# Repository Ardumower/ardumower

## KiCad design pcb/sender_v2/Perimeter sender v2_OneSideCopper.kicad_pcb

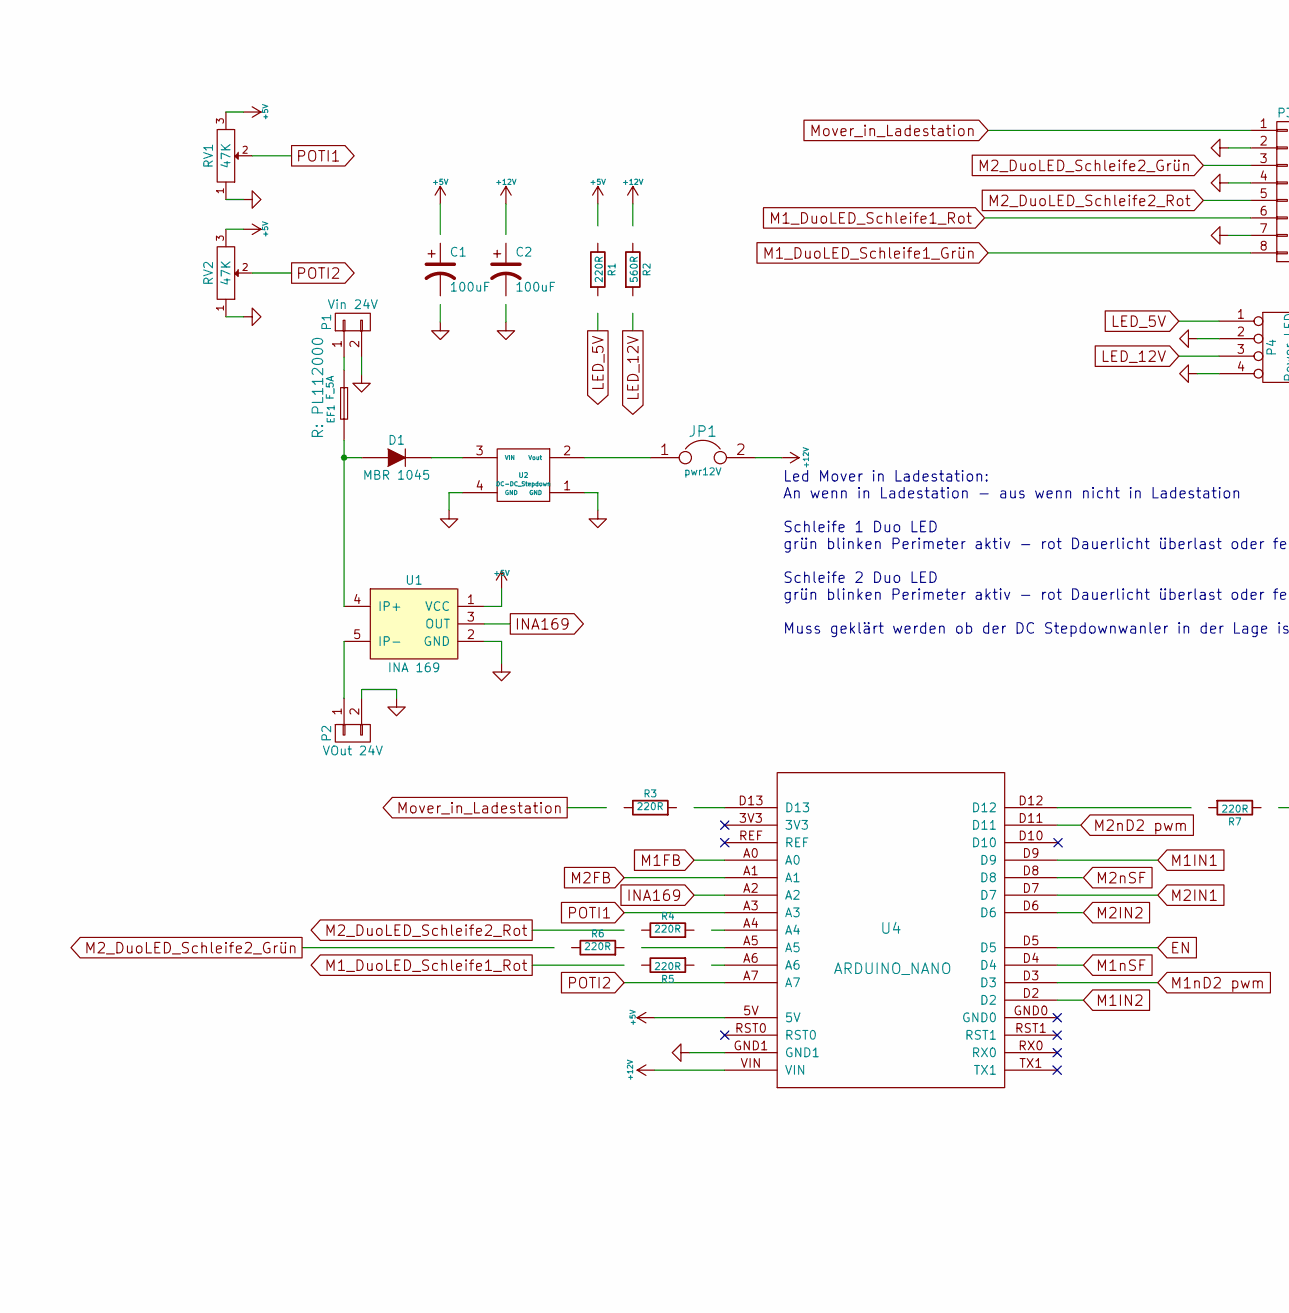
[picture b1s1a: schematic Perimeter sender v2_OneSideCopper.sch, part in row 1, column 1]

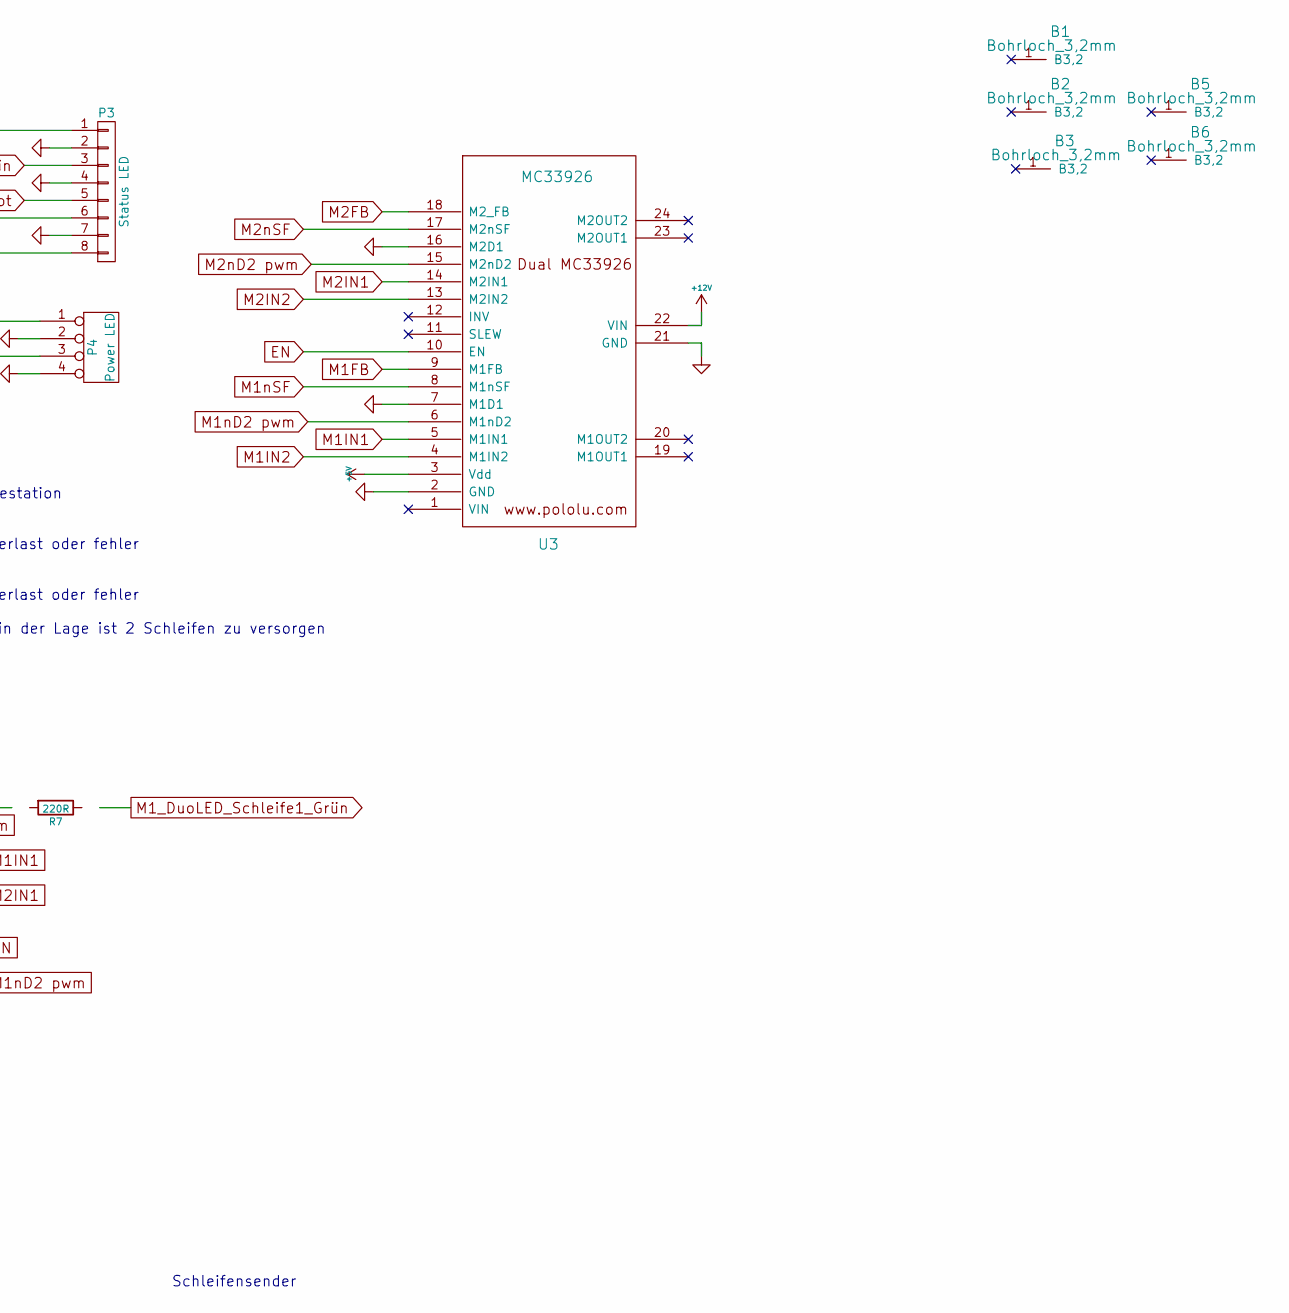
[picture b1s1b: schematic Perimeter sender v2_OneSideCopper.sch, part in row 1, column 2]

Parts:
B1, B2, B3, B5, B6: Bohrloch_3,2mm
C1, C2: 100uF; Elko_vert_11.2x6.3mm_RM2.5_RM5.0
D1: MBR 1045; MBR1045_Horizontal
EF1: F_5A; Fuseholder_Reichelt_PL112000
JP1: pwr12V; Pin_Header_Straight_1x02
P1: Vin 24V; Anschlussklemme_2P_RM5,08
P2: VOut 24V; Anschlussklemme_2P_RM5,08
P3: Status LED; Pin_Header_Straight_1x08
P4: Power LED; Pin_Header_Straight_1x04
R1, R3, R4, R5, R6, R7: 220R; Resistor_Horizontal_RM10mm
R2: 560R; Resistor_Horizontal_RM10mm
RV1, RV2: 47K; Potentiometer_VishaySpectrol-Econtrim-Type36T_3D-angepasst_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
U1: INA 169; INA169
U2: DC-DC_Stepdown; DC_DC_DSN2596_mit_Bohrloch
U3: MC33926; MC_33926_31polig_mit_Bohrloch_neue_Masse
U4: ARDUINO_NANO; arduino_nano

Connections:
+5V: C1.1, R1.1, RV1.3, RV2.3, U1.1 (VCC), U3.3 (Vdd), U4.5V
+12V: C2.1, JP1.2, R2.1, U3.22 (VIN), U4.VIN
EN: U3.10 (EN), U4.D5
GND: C1.2, C2.2, P1.2, P2.2, P3.2, P3.4, P3.7, P4.2, P4.4, RV1.1, RV2.1, U1.2 (GND), U2.1 (GND), U2.4 (GND), U3.2 (GND), U3.7 (M1D1), U3.16 (M2D1), U3.21 (GND), U4.GND1
INA169: U1.3 (OUT), U4.A2
LED_5V: P4.1, R1.2
LED_12V: P4.3, R2.2
M1FB: U3.9 (M1FB), U4.A0
M1IN1: U3.5 (M1IN1), U4.D9
M1IN2: U3.4 (M1IN2), U4.D2
M1_DuoLED_Schleife1_Grün: P3.8, R7.1
M1_DuoLED_Schleife1_Rot: P3.6, R5.1
M1nD2 pwm: U3.6 (M1nD2), U4.D3
M1nSF: U3.8 (M1nSF), U4.D4
M2FB: U3.18 (M2_FB), U4.A1
M2IN1: U3.14 (M2IN1), U4.D7
M2IN2: U3.13 (M2IN2), U4.D6
M2_DuoLED_Schleife2_Grün: P3.3, R6.1
M2_DuoLED_Schleife2_Rot: P3.5, R4.1
M2nD2 pwm: U3.15 (M2nD2), U4.D11
M2nSF: U3.17 (M2nSF), U4.D8
Mover_in_Ladestation: P3.1, R3.1
unnamed: D1.1 (A), EF1.1, U1.4 (IP+)
unnamed: D1.2 (K), U2.3 (VIN)
unnamed: EF1.2, P1.1
unnamed: JP1.1, U2.2 (Vout)
unnamed: P2.1, U1.5 (IP-)
unnamed: R3.2, U4.D13
unnamed: R4.2, U4.A4
unnamed: R5.2, U4.A6
unnamed: R6.2, U4.A5
unnamed: R7.2, U4.D12
POTI1: RV1.2, U4.A3
POTI2: RV2.2, U4.A7

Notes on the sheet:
Led Mover in Ladestation: An wenn in Ladestation - aus wenn nicht in Ladestation Schleife 1 Duo LED grün blinken Perimeter aktiv - rot Dauerlicht überlast oder fehler Schleife 2 Duo LED grün blinken Perimeter aktiv - rot Dauerlicht überlast oder fehler Muss geklärt werden ob der DC Stepdownwanler i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
Schleifensender

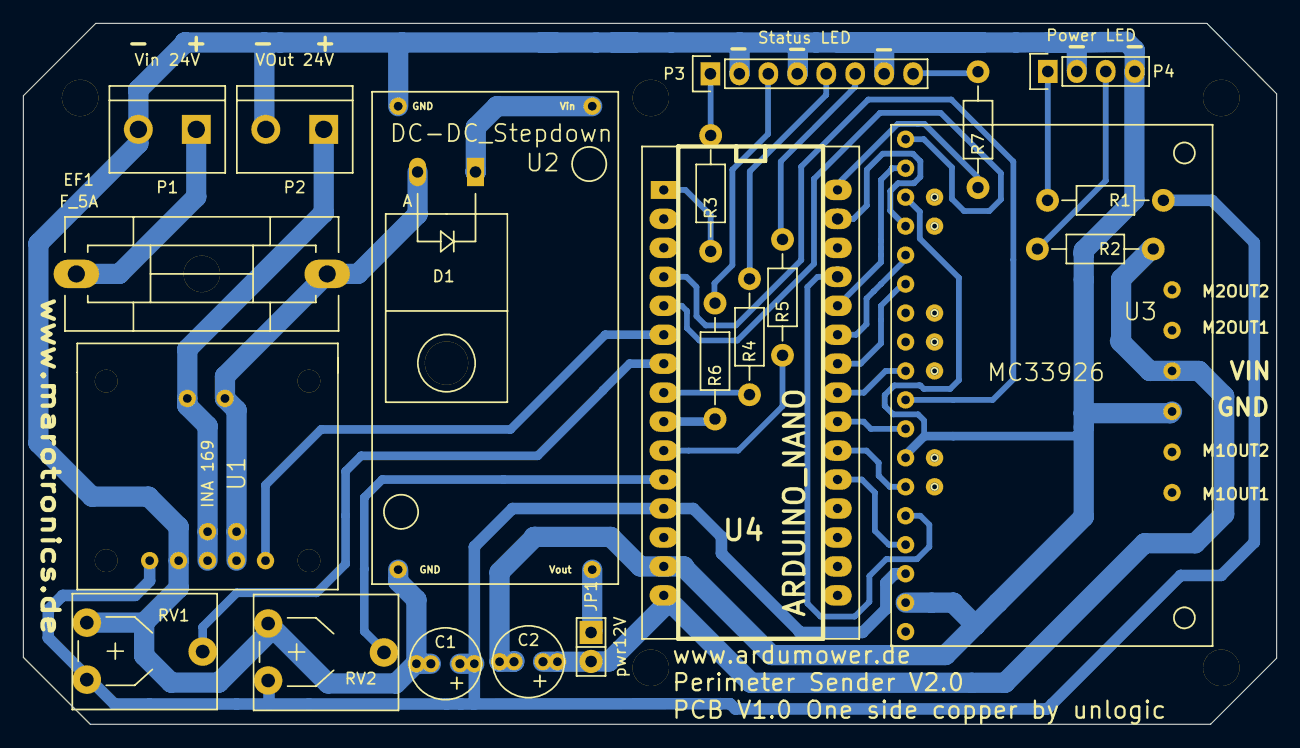
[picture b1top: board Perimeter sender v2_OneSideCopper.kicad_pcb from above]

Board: 2 copper layers, 109.9 x 61.5 mm, 27 parts (0 on the bottom side), 34 nets.

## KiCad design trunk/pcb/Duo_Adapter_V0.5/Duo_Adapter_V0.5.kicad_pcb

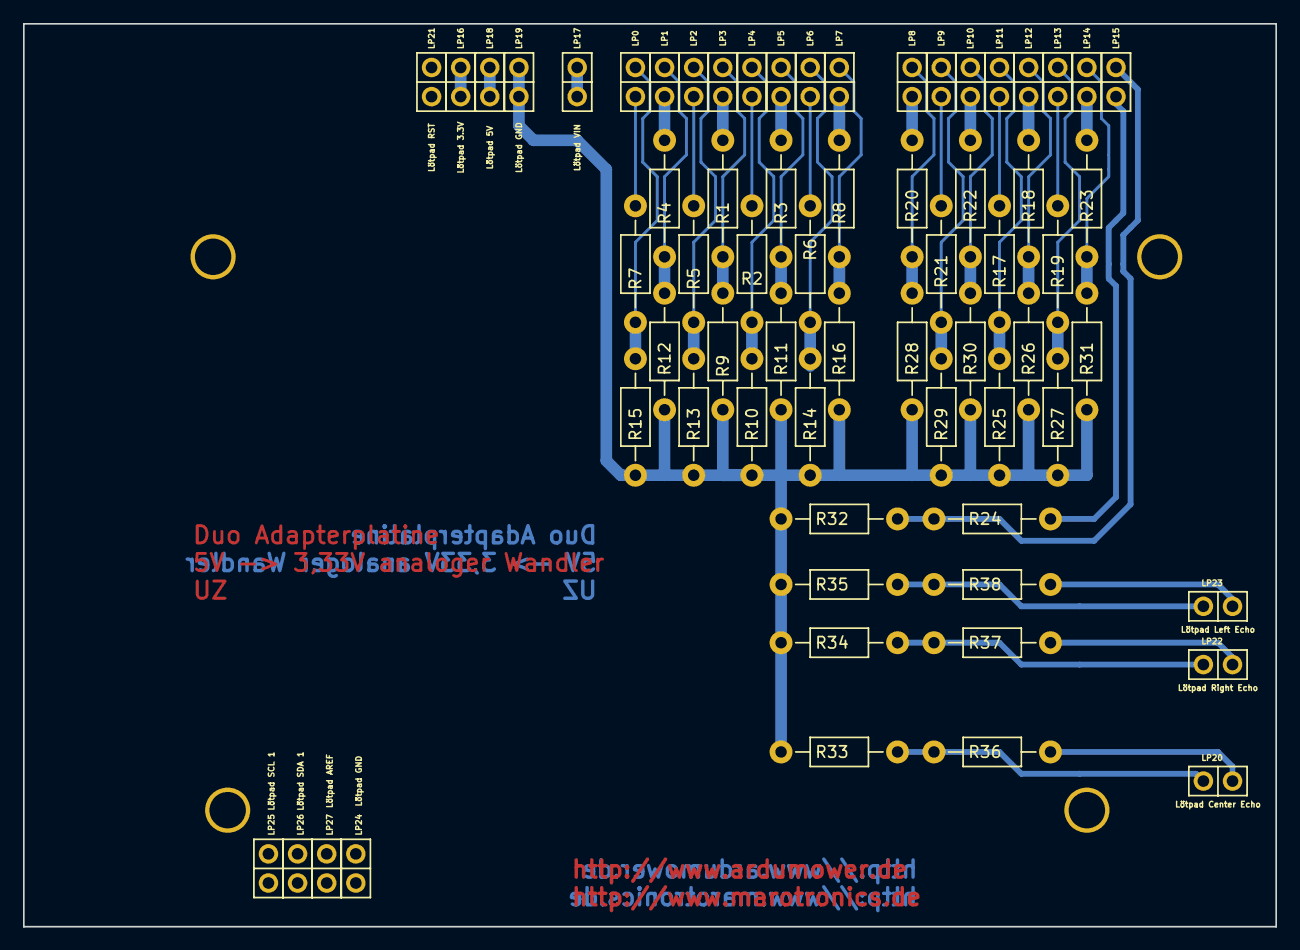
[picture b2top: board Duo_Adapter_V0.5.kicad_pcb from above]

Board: 2 copper layers, 109.2 x 78.7 mm, 67 parts (1 on the bottom side), 42 nets.

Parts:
LP0, LP1, LP2, LP3, LP4, LP5, LP6, LP7, LP8, LP9, LP10, LP11, LP12, LP13, LP14, LP15: Lötpad; Lötpad_1x02_Buchse
LP16: Lötpad 3.3V; Lötpad_1x02_Buchse
LP17: Lötpad VIN; Lötpad_1x02_Buchse
LP18: Lötpad 5V; Lötpad_1x02_Buchse
LP19, LP24: Lötpad GND; Lötpad_1x02_Buchse
LP20: Lötpad Center Echo; Lötpad_1x02_Buchse
LP21: Lötpad RST; Lötpad_1x02_Buchse
LP22: Lötpad Right Echo; Lötpad_1x02_Buchse
LP23: Lötpad Left Echo; Lötpad_1x02_Buchse
LP25: Lötpad SCL 1; Lötpad_1x02_Buchse
LP26: Lötpad SDA 1; Lötpad_1x02_Buchse
LP27: Lötpad AREF; Lötpad_1x02_Buchse
R1, R2, R3, R4, R5, R6, R7, R8, R17, R18, R19, R20, R21, R22, R23, R24, R36, R37, R38: R 10K; Resistor_Horizontal_RM10mm
R9, R10, R11, R12, R13, R14, R15, R16, R25, R26, R27, R28, R29, R30, R31, R32, R33, R34, R35: R 20K; Resistor_Horizontal_RM10mm
SHIELD1: ARDUINO_MEGA_SHIELD; ARDUINO_MEGA_SHIELD_DUO_3D

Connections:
+3V3: LP16.1, LP16.2
+5V: LP18.1, LP18.2
GND: LP19.1, LP19.2, R9.2, R10.2, R11.2, R12.2, R13.2, R14.2, R15.2, R16.2, R25.2, R26.2, R27.2, R28.2, R29.2, R30.2, R31.2, R32.2, R33.2, R34.2, R35.2
unnamed: LP0.1, R7.1
unnamed: LP0.2, R7.2, R15.1
unnamed: LP1.1, R4.1
unnamed: LP1.2, R4.2, R12.1
unnamed: LP2.1, R5.1
unnamed: LP2.2, R5.2, R13.1
unnamed: LP3.1, R1.1
unnamed: LP3.2, R1.2, R9.1
unnamed: LP4.1, R2.1
unnamed: LP4.2, R2.2, R10.1
unnamed: LP5.1, R3.1
unnamed: LP5.2, R3.2, R11.1
unnamed: LP6.1, R6.1
unnamed: LP6.2, R6.2, R14.1
unnamed: LP7.1, R8.1
unnamed: LP7.2, R8.2, R16.1
unnamed: LP8.1, R20.1
unnamed: LP8.2, R20.2, R28.1
unnamed: LP9.1, R21.1
unnamed: LP9.2, R21.2, R29.1
unnamed: LP10.1, R22.1
unnamed: LP10.2, R22.2, R30.1
unnamed: LP11.1, R17.1
unnamed: LP11.2, R17.2, R25.1
unnamed: LP12.1, R18.1
unnamed: LP12.2, R18.2, R26.1
unnamed: LP13.1, R19.1
unnamed: LP13.2, R19.2, R27.1
unnamed: LP14.1, R23.1
unnamed: LP14.2, R23.2, R31.1
unnamed: LP15.1, R24.1
unnamed: LP15.2, R24.2, R32.1
unnamed: LP17.1, LP17.2
unnamed: LP20.1, R33.1, R36.2
unnamed: LP20.2, R36.1
unnamed: LP22.1, R34.1, R37.2
unnamed: LP22.2, R37.1
unnamed: LP23.1, R35.1, R38.2
unnamed: LP23.2, R38.1

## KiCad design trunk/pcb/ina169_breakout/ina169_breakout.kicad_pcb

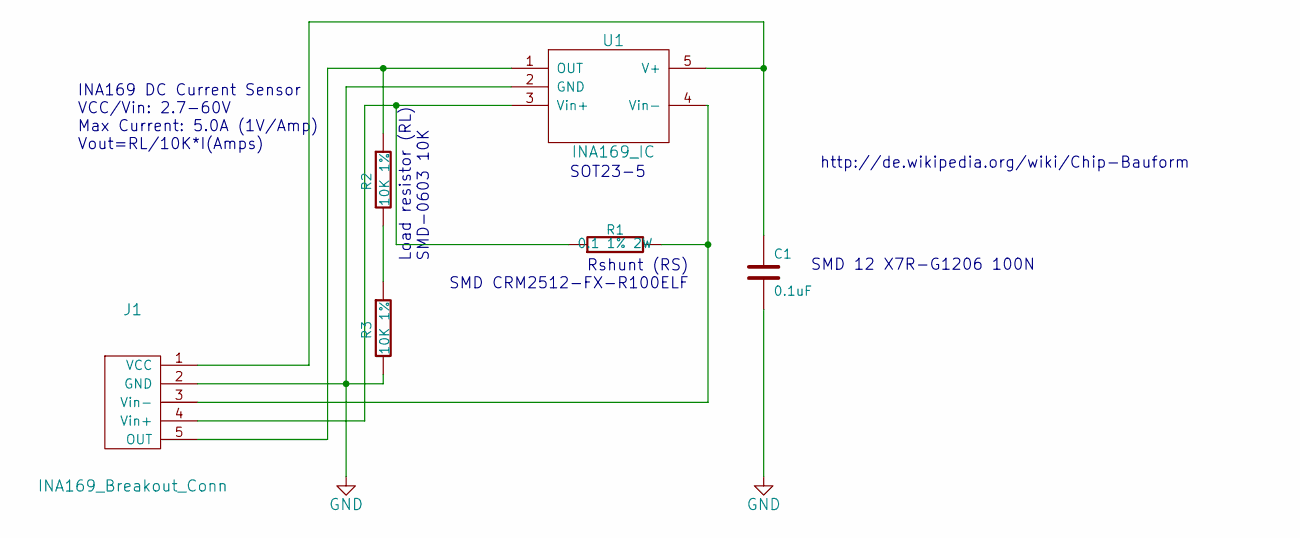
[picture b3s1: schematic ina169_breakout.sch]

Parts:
C1: 0.1uF; C_1206
J1: INA169_Breakout_Conn; ina169_breakout_footprint
R1: 0.1 1% 2W; R_2512
R2, R3: 10K 1%; R_0603
U1: INA169_IC; ina169_ic_sot23-5

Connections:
GND: C1.2, J1.2 (GND), R3.2, U1.2 (GND)
unnamed: C1.1, J1.1 (VCC), U1.5 (V+)
unnamed: J1.3 (Vin-), R1.2, U1.4 (Vin-)
unnamed: J1.4 (Vin+), R1.1, U1.3 (Vin+)
unnamed: J1.5 (OUT), R2.1, U1.1 (OUT)
unnamed: R2.2, R3.1

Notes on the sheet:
Rshunt (RS) SMD CRM2512-FX-R100ELF
Load resistor (RL) SMD-0603 10K
INA169 DC Current Sensor VCC/Vin: 2.7-60V Max Current: 5.0A (1V/Amp) Vout=RL/10K*I(Amps)
SMD 12 X7R-G1206 100N
SOT23-5
http://de.wikipedia.org/wiki/Chip-Bauform

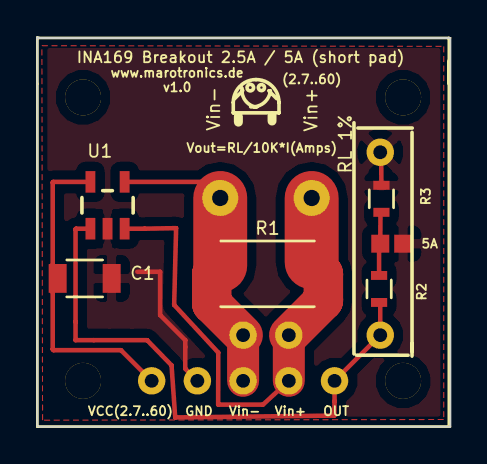
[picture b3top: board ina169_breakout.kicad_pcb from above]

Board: 2 copper layers, 23.0 x 21.7 mm, 6 parts (0 on the bottom side), 6 nets.

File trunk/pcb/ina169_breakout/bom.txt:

C1  0.1uF  1206   SMD 12 X7R-G1206 100N        
R1  0.1  1%  2W   2512  SMD CRM2512-FX-R100ELF  
R2,R3   10K  1%   0603  
U1   INA169 SOT23-5

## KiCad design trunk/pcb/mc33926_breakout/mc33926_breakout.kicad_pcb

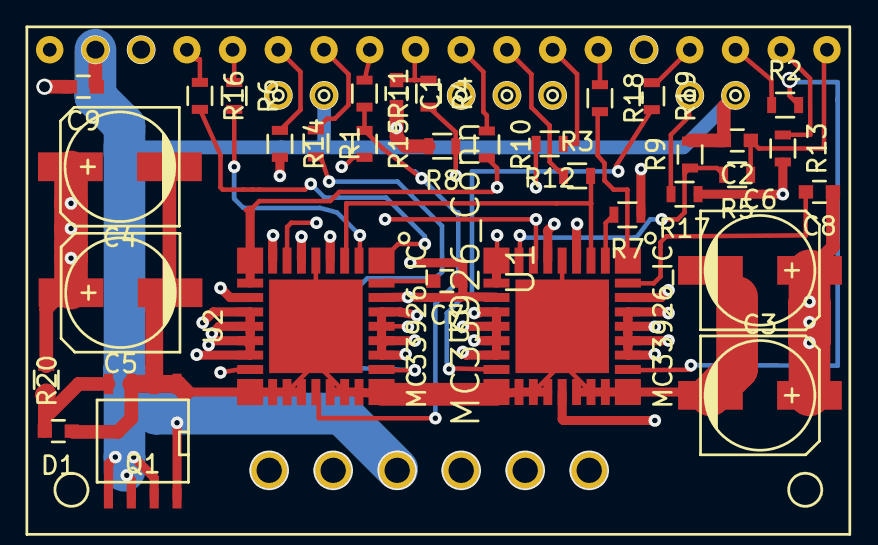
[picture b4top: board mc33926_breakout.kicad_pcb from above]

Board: 4 copper layers, 34 parts (0 on the bottom side), 41 nets.

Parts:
C1, C2: 0.47uF; C_0603
C3, C4, C5, C6: 47uF; c_elec_6.3x5.8
C7, C8: 33nF; C_0603
C9: 0.1uF; C_0603
D1: ZENER; C_0603
Q1: MOSN-SO8; SOIC-8-N
R1, R2, R3, R4, R5, R6, R7, R10, R11, R12, R13, R14, R16, R18, R19: 1k; R_0603
R8, R9: 220; R_0603
R15, R17: 10k; R_0603
R20: 100k; R_0603
U1: MC33926_Conn; mc33926_breakout_footprint
U2, U3: MC33926_IC; mc33926_ic_pqfn32

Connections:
ENP: R10.2, U2.9, U2.10, U3.9, U3.10
FGND: C3.2, C4.2, C5.2, C6.2, D1.1, Q1.1, Q1.2, Q1.3, U2.5, U2.17, U2.18, U2.19, U2.20, U2.22, U2.23, U2.24, U2.25, U2.33, U3.5, U3.17, U3.18, U3.19, U3.20, U3.22, U3.23, U3.24, U3.25, U3.33
GND: C1.2, C2.2, C9.1, Q1.5, Q1.6, Q1.7, Q1.8, R8.2, R9.2, U1.2, U1.21
INVP: R12.2, U2.7, U3.7
M1OUT1: U1.19, U2.12, U2.13, U2.14, U2.15
M1OUT2: U1.20, U2.27, U2.28, U2.29, U2.30
M2OUT1: U1.23, U3.12, U3.13, U3.14, U3.15
M2OUT2: U1.24, U3.27, U3.28, U3.29, U3.30
unnamed: C1.1, R4.1, U1.9
unnamed: C2.1, R5.1, U1.18
unnamed: C7.2, U2.32
unnamed: C8.2, U3.32
unnamed: D1.2, Q1.4, R20.1
unnamed: R1.1, U1.7
unnamed: R1.2, U2.26
unnamed: R2.1, U1.16
unnamed: R2.2, U3.26
unnamed: R3.1, U1.11
unnamed: R4.2, R8.1, U2.8
unnamed: R5.2, R9.1, U3.8
unnamed: R6.1, U1.5
unnamed: R6.2, U2.2
unnamed: R7.1, U1.14
unnamed: R7.2, U3.2
unnamed: R10.1, U1.10
unnamed: R11.1, U1.8
unnamed: R11.2, R15.1, U2.21
unnamed: R12.1, U1.12
unnamed: R13.1, U1.17
unnamed: R13.2, R17.1, U3.21
unnamed: R14.1, U1.6
unnamed: R14.2, U2.16
unnamed: R16.1, U1.4
unnamed: R16.2, U2.1
unnamed: R18.1, U1.13
unnamed: R18.2, U3.1
unnamed: R19.1, U1.15
unnamed: R19.2, U3.16
SLEWP: R3.2, U2.3, U3.3
VIN: C3.1, C4.1, C5.1, C6.1, C7.1, C8.1, C9.2, R20.2, U1.1, U1.22, U2.4, U2.6, U2.11, U2.31, U3.4, U3.6, U3.11, U3.31
Vdd: R15.2, R17.2, U1.3

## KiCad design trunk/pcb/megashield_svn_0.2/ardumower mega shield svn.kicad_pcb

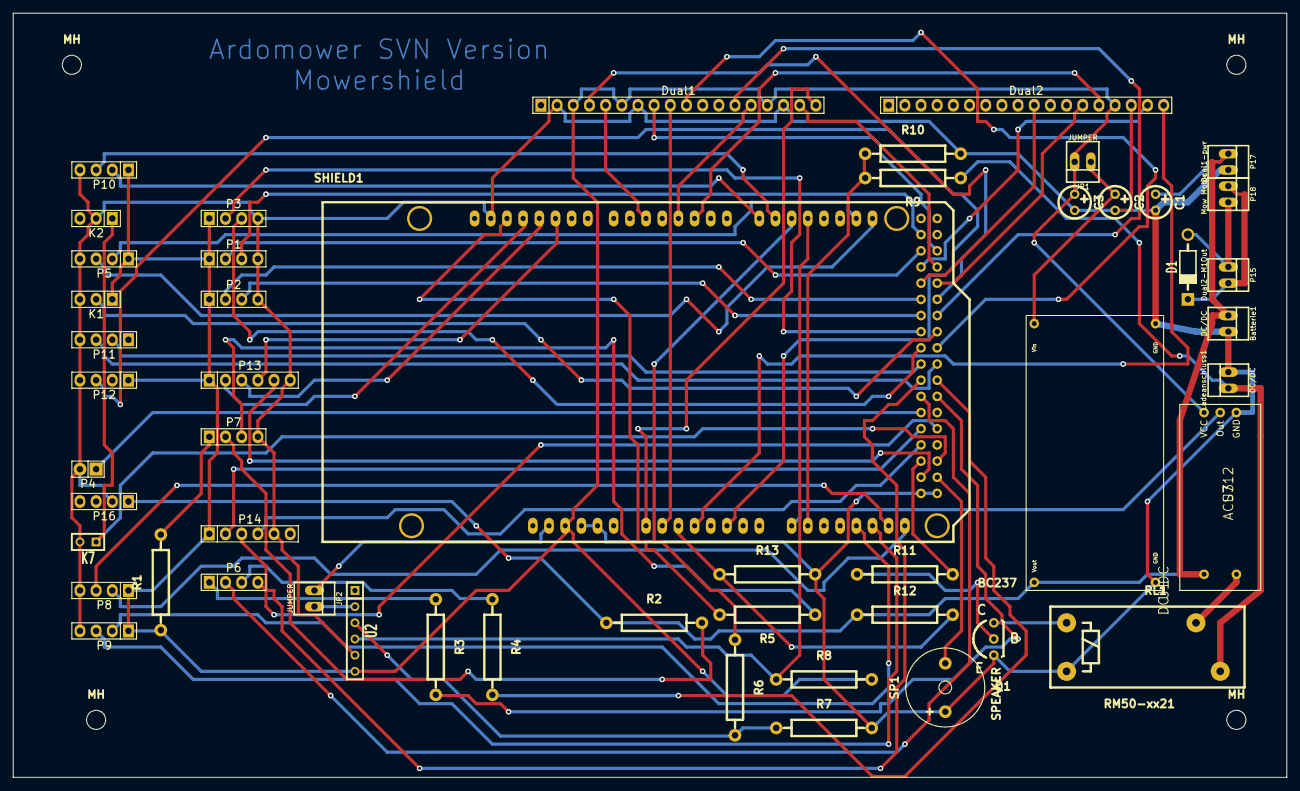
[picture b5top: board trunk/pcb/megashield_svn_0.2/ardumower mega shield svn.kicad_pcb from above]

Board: 2 copper layers, 200.0 x 120.0 mm, 55 parts (0 on the bottom side), 71 nets.

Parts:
Batterie1: DC/DC; PINHEAD1-2
C1, C2: 10uF; Elko_vert_DM5_RM2-5
C3: 0,1uF; Elko_vert_DM5_RM2-5
D1: MBR1045 schotky; Diode_DO-41_SOD81_Horizontal_RM10
Dual1, Dual2: MC33926; Pin_Header_Straight_1x18
JP1, JP2: JUMPER; PINHEAD1-2
K1: Tilt sens; Pin_Header_Straight_1x03
K2: CONN_01X02; Pin_Header_Straight_1x03
K7: CONN_01X02; SIL-2
Ladeanschluss1: DC/DC; PINHEAD1-2
MH: MountingHole_3mm_RevA_Date21Jun2010; MountingHole_3mm
MH#2, MH#3, MH#4: MountingHole_3mm_RevA_Date21Jun2010; MountingHole_3mm
P1: Sonar C; Pin_Header_Straight_1x04
P2: Sonar R; Pin_Header_Straight_1x04
P3: Sonar L; Pin_Header_Straight_1x04
P4: Rain; Pin_Header_Straight_1x02
P5: I2C; Pin_Header_Straight_1x04
P6: Lawn sens; Pin_Header_Straight_1x04
P7: CONN_01X04; Pin_Header_Straight_1x04
P8: ODO Right; Pin_Header_Straight_1x04
P9: ODO Left; Pin_Header_Straight_1x04
P10: GPS; Pin_Header_Straight_1x04
P11: Bumper; Pin_Header_Straight_1x04
P12: Perimeter; Pin_Header_Straight_1x04
P13: RC Remote; Pin_Header_Straight_1x06
P14: User switch; Pin_Header_Straight_1x06
P15: Dual2-M1Out; PINHEAD1-2
P16: Dual2-pwr; Pin_Header_Straight_1x04
P17: Dual1-pwr; PINHEAD1-2
P18: Mow Motor; PINHEAD1-2
Q1: BC237; TO-92-Bipolar-inline-wide-EBC
R1: 470r; Resistor_Horizontal_RM15mm
R2, R11: 2k2; Resistor_Horizontal_RM15mm
R3, R4: 2M2; Resistor_Horizontal_RM15mm
R5, R6: 470R; Resistor_Horizontal_RM15mm
R7, R8: 1K; Resistor_Horizontal_RM15mm
R9, R12: 47K; Resistor_Horizontal_RM15mm
R10, R13: 5K; Resistor_Horizontal_RM15mm
RL1: RM50-xx21; Relais_SPDT_Schrack-RP-II-1_RM3-5mm
SHIELD1: ARDUINO_MEGA_SHIELD; ARDUINO MEGA SHIELD
SP1: SPEAKER; Buzzer_12x9.5RM7.6
U1: DC-DC
U2: HC05_MODULE_ardumower_; SIL-6
U3: ACS712; ACS712BreakOut

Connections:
+3.3V: JP2.1, SHIELD1.3V3
+5V: C3.1, Dual1.3, Dual1.6, Dual1.15, Dual2.15, JP1.2, K1.1, P1.1, P2.1, P3.1, P5.1, P8.1, P9.1, P10.1, P12.1, P13.1, P14.1, R1.1, R8.2, SHIELD1.5V, U2.6, U3.1
+24V: Batterie1.1, C1.1, P16.1, P17.1, R2.1, R12.1, U1.3, U3.4
GND: Batterie1.2, C1.2, C2.2, C3.2, Dual1.2, Dual1.7, Dual1.16, Dual2.16, K1.3, K2.2, K7.2, Ladeanschluss1.2, P1.4, P2.4, P3.4, P4.2, P5.4, P7.4, P8.4, P9.4, P10.4, P11.4, P12.4, P13.6, P14.5, P16.2, P17.2, Q1.E, R7.2, R10.2, R13.2, RL1.A2, SHIELD1.GND1, SHIELD1.GND2, SHIELD1.GND3, SHIELD1.GND4, SHIELD1.GND5, SP1.1, U1.1, U1.4, U2.5, U3.2
GPS_RX: P10.2, SHIELD1.14
GPS_TX: P10.3, SHIELD1.15
Led-Status: P7.3, R5.1
LedPin-5v: P7.1, R1.2
LedPin-24v: P7.2, R2.2
unnamed: C2.1, JP1.1, U1.2
unnamed: D1.1, P15.1, P18.2
unnamed: D1.2, P15.2, P18.1
unnamed: JP2.2, U2.2
unnamed: Ladeanschluss1.1, R9.1, RL1.14
unnamed: P6.1, R3.1
unnamed: P6.3, R4.1
unnamed: Q1.B, R11.1
unnamed: Q1.C, RL1.A1
unnamed: R6.2, R7.1, U2.3
unnamed: RL1.11, U3.5
RX2: R8.1, SHIELD1.17, U2.4
SCL: P5.3, SHIELD1.21
SDA: P5.2, SHIELD1.20
TX2: R6.1, SHIELD1.16
pinBatteryVoltage: R12.2, R13.1, SHIELD1.AD2
pinBumperLeft: P11.3, SHIELD1.39
pinBumperRight: P11.2, SHIELD1.38
pinButton: K2.1, K7.1, SHIELD1.51
pinBuzzer: SHIELD1.53, SP1.2
pinChargeCurrent: SHIELD1.AD8, U3.3
pinChargeVoltage: R9.2, R10.1, SHIELD1.AD9
pinChargingEnable: R11.2, SHIELD1.50
pinLawnBackRecv: P6.2, SHIELD1.42
pinLawnBackSend: R3.2, SHIELD1.43
pinLawnFrontRecv: P6.4, SHIELD1.40
pinLawnFrontSend: R4.2, SHIELD1.41
pinLed: R5.2, SHIELD1.13
pinMotorEnable: Dual1.10, SHIELD1.37
pinMotorLeftDir: Dual1.4, SHIELD1.31
pinMotorLeftFault: Dual1.8, SHIELD1.25
pinMotorLeftPWM: Dual1.5, SHIELD1.5
pinMotorLeftSense: Dual1.9, SHIELD1.AD1
pinMotorMowDir: Dual2.13, SHIELD1.29
pinMotorMowEnable: Dual2.10, SHIELD1.28
pinMotorMowFault: Dual2.17, SHIELD1.26
pinMotorMowPWM: Dual2.14, SHIELD1.2
pinMotorMowSense: Dual2.18, SHIELD1.AD3
pinMotorRightDir: Dual1.13, SHIELD1.33
pinMotorRightFault: Dual1.17, SHIELD1.27
pinMotorRightPWM: Dual1.14, SHIELD1.3
pinMotorRightSense: Dual1.18, SHIELD1.AD0
pinOdometryLeft: P9.2, SHIELD1.AD12
pinOdometryLeft2: P9.3, SHIELD1.AD13
pinOdometryRight: P8.2, SHIELD1.AD15
pinOdometryRight2: P8.3, SHIELD1.AD14
pinPerimeterLeft: P12.3, SHIELD1.AD5
pinRain: P4.1, SHIELD1.44
pinRemoteMow: P13.2, SHIELD1.12
pinRemoteSpeed: P13.4, SHIELD1.10
pinRemoteSteer: P13.3, SHIELD1.11
pinRemoteSwitch: P13.5, SHIELD1.52
pinSonarCenterEcho: P1.3, SHIELD1.22
pinSonarCenterTrigger: P1.2, SHIELD1.24
pinSonarLeftEcho: P3.3, SHIELD1.36
pinSonarLeftTrigger: P3.2, SHIELD1.34
pinSonarRightEcho: P2.3, SHIELD1.32
pinSonarRightTrigger: P2.2, SHIELD1.30
pinTilt: K1.2, SHIELD1.35
pinUserSwitch1: P14.2, SHIELD1.46
pinUserSwitch2: P14.3, SHIELD1.47
pinUserSwitch3: P14.4, SHIELD1.48

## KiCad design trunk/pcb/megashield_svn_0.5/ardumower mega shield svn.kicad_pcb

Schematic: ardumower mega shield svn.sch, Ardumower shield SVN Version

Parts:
B1, B2, B3, B4, B5, B6, B7, B8: Bohrloch_3,2mm
C1, C4: 1uF; Elko_vert_11.2x6.3mm_RM2.5_RM5.0
C2, C7, C8: 100uF; Elko_vert_11.2x6.3mm_RM2.5_RM5.0
C3, C6: 1,0uF; Elko_vert_11.2x6.3mm_RM2.5_RM5.0
C5: 1000uF; Elko_vert_31.5x16mm_RM7.5
D1, D4: MBR 1045; MBR1045
D2: 1,5KE 30A ?; Diode_ligend_RM10
D3: MPR 1045; MBR1045
D5, D6: 1N4148; Diode_ligend_RM10
D7: 1N4007; Diode_ligend_RM10
D8: BlueLED; Diode_LED_5mm_round_vertical
D9: MBR 1045; MBR1045_liegend
D10: 1,5KE 30A; Diode_ligend_RM10
Dual1, Dual2: MC33926; MC_33926_31polig_mit_Bohrloch_neue_Masse
EF1, EF2: F_10A; Fuseholder_Reichelt_PL112000
JP1: pwr 10V; Pin_Header_Straight_1x02
JP2: Key; Pin_Header_Straight_1x02
JP3: pwrAA3,3; Pin_Header_Straight_1x02
JP4: R-Arduino; Pin_Header_Straight_1x02
JP5: R-GND; Pin_Header_Straight_1x02
JP6, JP7: V-A-Relais; Pin_Header_Straight_1x02
JP8: Blue5.0V; Pin_Header_Straight_1x02
JP9: Blue3.3V; Pin_Header_Straight_1x02
JP10: pwr 3,3V; Pin_Header_Straight_1x02
JP11: pwr 5V; Pin_Header_Straight_1x02
JP12: pwrAA5.0V; Pin_Header_Straight_1x02
JP13: Mess3.3V; Pin_Header_Straight_1x02
JP14: Mess5.0V; Pin_Header_Straight_1x02
JP15: MessA3.3V; Pin_Header_Straight_1x02
K3: RELAY_2RT; Relais_DPDT_Schrack-RT2_RM5mm_3D_Kontaktbelegung_geändert_F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
LP0, LP1, LP2, LP3, LP4, LP5, LP6, LP7, LP8, LP9, LP10, LP11, LP12, LP13, LP14, LP15, LP16, LP17, LP18, LP19, LP20, LP21, LP22, LP23, LP24, LP25, LP26, LP27: Lötpad; Lötpad_1x02
P1: Sonar C; Pin_Header_Straight_1x04
P2: Sonar R; Pin_Header_Straight_1x04
P3: Sonar L; Pin_Header_Straight_1x04
P4: Res.AD11; Pin_Header_Straight_1x03
P5: IMU Kompas; Pin_Header_Straight_1x04
P6: Lawn sens; Pin_Header_Straight_1x04
P7: Status LEDs; Pin_Header_Straight_1x08
P8: ODO Right; Pin_Header_Straight_1x04
P9: ODO Left; Pin_Header_Straight_1x04
P10: GPS; Pin_Header_Straight_1x04
P11: Bumper; Pin_Header_Straight_1x04
P12: P.Left; Pin_Header_Straight_1x03
P13: RC Remote; Pin_Header_Straight_1x06
P14: Mess V; Pin_Header_Straight_1x03
P15: Links; PINHEAD1-2
P16, P17: V.OUT; PINHEAD1-2
P18: Rechts; PINHEAD1-2
P19: Tilt sens; Pin_Header_Straight_1x03
P20: Button; Pin_Header_Straight_1x02
P21: DropRight; Pin_Header_Straight_1x03
P22: Res.AD6; Pin_Header_Straight_1x03
P23: I2C Res.1; Pin_Header_Straight_1x05
P24: I2C Res.2; Pin_Header_Straight_1x05
P25: Res.Pin9; Pin_Header_Straight_1x03
P26: Res.Pin4; Pin_Header_Straight_1x03
P27: Res.Pin0; Pin_Header_Straight_1x03
P28: Res.Pin8; Pin_Header_Straight_1x03
P29: Res.Pin1; Pin_Header_Straight_1x03
P30: P.Right; Pin_Header_Straight_1x03
P31: DropLeft; Pin_Header_Straight_1x03
P32: Stromleiste GND; Pin_Header_Straight_1x08
P33: Stromleiste 5V; Pin_Header_Straight_1x08
P34: Stromleiste 3,3V; Pin_Header_Straight_1x08
P35: MowRpm; Pin_Header_Straight_1x03
P36: RES. M1; PINHEAD1-2
P37: Mähteller; PINHEAD1-2
P38: Res24V-2; Aschlussklemme_2p_3D
P39: Res24V-1; Aschlussklemme_2p_3D
P40: UserSwitsch; Pin_Header_Straight_1x05
P41: Rain; Pin_Header_Straight_1x03
P42: Ladeanschluss; Aschlussklemme_2p_3D
P43: Akku; Aschlussklemme_2p_3D
P44: Wlan; Pin_Header_Straight_1x05
P45: I2C Res.3; Pin_Header_Straight_1x05
P46: I2C Res.4; Pin_Header_Straight_1x05
Q1: BC237; TO92-EBC
R1: 220; Resistor_Horizontal_RM15mm
R2, R11: 1K5; Resistor_Horizontal_RM10mm
R3, R4: 2M2; Resistor_Horizontal_RM10mm
R5, R20, R21: 220R; Resistor_Horizontal_RM15mm
R6, R15: 470R; Resistor_Horizontal_RM15mm
R7, R8, R14, R16: 1K; Resistor_Horizontal_RM15mm
R9: 47K; Resistor_Horizontal_RM10mm
R10: 4,99K; Resistor_Horizontal_RM10mm
R12: 47K; Resistor_Horizontal_RM15mm
R13: 4,99K; Resistor_Horizontal_RM15mm
R17: 240; Resistor_Horizontal_RM15mm
R18: 2k2; Resistor_Horizontal_RM15mm
R19: ????; Resistor_Horizontal_RM15mm
R22: 120; Resistor_Horizontal_RM15mm
R23: 100; Resistor_Horizontal_RM15mm
R24, R25, R26: ??; Resistor_Horizontal_RM15mm
RP1, RP2: 150; DIP-16__300
RR1, RR2: C0,1uF; Kondensatorenleiste_8er_9pin_3D
RV1: 5K; Potentiometer_VishaySpectrol-Econtrim-Type36T_3D
SHIELD1: ARDUINO_MEGA_SHIELD; ARDUINO_MEGA_SHIELD_DUO_3D
SP1: SPEAKER; Buzzer_12x9.5RM7.6_RM5.0
U1: DC 10V; DC_DC_DSN2596_mit_Bohrloch
U2: Bluetooth_CZ_HC_05; Bluetooth_Buchse_Platz
U3, U5: INA169 Adafruit; INA169
U4: LM350T; LM350T_3D_muss_noch_auf_Masse_geprüft_werden
U6: DC 3,3V; DC_DC_DSN2596_mit_Bohrloch
U7: DC 5V; DC_DC_DSN2596_mit_Bohrloch
U8: DS1307+; Tiny_RTC_DS1307_geändert_mit_Bohrloch
U9: Wlan_ESP8266; Wlan_ESP8266_3D
U10: I2C_5-3V
U11: Wlan_ESP8266 Rückseite; Wlan_ESP8266_3D
ZD1: ZD-5W 3,3V; Diode_ligend_RM10
ZD2: ZD-5W 5,1; Diode_ligend_RM10
ZD3: ZD-5W 12V; Diode_ligend_RM10

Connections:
+3.3V: JP2.1, JP3.1, JP9.1, JP10.2, JP13.1, P23.5, P24.5, P34.1, P34.2, P34.3, P34.4, P34.5, P34.6, P34.7, P34.8, P44.5, P45.5, P46.5, R23.1, U9.4 (VCC), U10.5, U11.4 (VCC)
DropLeft: D5.1 (A), SHIELD1.45 (PL4)
DropRight: D6.1 (A), SHIELD1.23 (PA1)
DuoLED-Rot: P7.7, R20.2
DuoLED_Grün: P7.6, R21.2
GND: C1.2, C2.2, C3.2, C4.2, C5.2, C6.2, C7.2, C8.2, D8.2, Dual1.2 (GND), Dual1.7 (M1D1), Dual1.16 (M2D1), Dual1.21 (GND), Dual2.2 (GND), Dual2.16 (M2D1), Dual2.21 (GND), JP5.1, LP19.1, LP19.2, LP24.1, LP24.2, P1.2, P2.2, P3.2, P4.2 (PM), P5.2, P7.1, P8.2, P9.2, P10.2, P11.1, P11.2, P12.2 (PM), P13.2, P14.2 (PM), P16.1, P17.1, P19.2 (PM), P20.2, P21.2 (PM), P22.2 (PM), P23.2, P24.2, P25.2 (PM), P26.2 (PM), P27.2 (PM), P28.2 (PM), P29.2 (PM), P30.2 (PM), P31.2 (PM), P32.1, P32.2, P32.3, P32.4, P32.5, P32.6, P32.7, P32.8, P35.2 (PM), P38.1, P39.1, P40.2, P41.2 (PM), P42.1, P43.1, P44.2, P45.2, P46.2, Q1.E, R7.2, R10.2, R13.2, R16.2, R24.2, R25.2, R26.2, RR1.1 (COM), RR2.1 (COM), RV1.2, RV1.3, SHIELD1.GND1, SHIELD1.GND2, SHIELD1.GND3, SHIELD1.GND4, SHIELD1.GND5, SP1.1, U1.1 (GND), U1.4 (GND), U2.2 (GND), U3.2 (GND), U5.2 (GND), U6.1 (GND), U6.4 (GND), U7.1 (GND), U7.4 (GND), U8.2 (GND), U9.5 (GND), U10.4, U10.8, U11.5 (GND)
GPS_RX: P10.3, SHIELD1.14 (TX3)
GPS_TX: P10.4, SHIELD1.15 (RX3)
Led-Status: P7.8, R5.2
LedPin-3V: P7.2, R23.2
LedPin-5v: P7.4, R1.2
LedPin-24v: P7.3, R2.2
unnamed: C1.1, D7.2 (K), U3.5 (IP-), U4.3 (IN)
unnamed: C2.1, JP1.1, U1.2 (Vout), ZD3.2 (K)
unnamed: C4.1, D3.1 (A), D7.1 (A), R17.1, U4.2 (OUT)
unnamed: C5.1, JP6.1, JP7.1, U5.4 (IP+)
unnamed: C7.1, JP10.1, U6.2 (Vout), ZD1.2 (K)
unnamed: C8.1, JP11.1, U7.2 (Vout), ZD2.2 (K)
unnamed: D1.1 (A), EF1.2, R19.1
unnamed: D1.2 (K), R9.1, R11.1, U3.4 (IP+)
unnamed: D2.1 (A), Dual2.23 (M2OUT1), P37.1
unnamed: D2.2 (K), Dual2.24 (M2OUT2), P37.2 (PM)
unnamed: D3.2 (K), K3.16 (T2)
unnamed: D4.1 (A), K3.1 (T1)
unnamed: D5.2 (K), P31.3
unnamed: D6.2 (K), P21.3
unnamed: D8.1, R22.2
unnamed: D10.1 (A), JP5.2, K3.9, Q1.C
unnamed: D10.2 (K), K3.8, R19.2
unnamed: Dual1.19 (M1OUT1), P15.1
unnamed: Dual1.20 (M1OUT2), P15.2 (PM)
unnamed: Dual1.23 (M2OUT1), P18.1
unnamed: Dual1.24 (M2OUT2), P18.2 (PM)
unnamed: Dual2.19 (M1OUT1), P36.1
unnamed: Dual2.20 (M1OUT2), P36.2 (PM)
unnamed: EF1.1, P42.2 (PM)
unnamed: EF2.2, P43.2 (PM)
unnamed: JP2.2, U2.5 (Key)
unnamed: JP4.2, R18.1
unnamed: JP6.2, K3.5 (C1), K3.12 (C2)
unnamed: JP8.2, JP9.2, U2.1 (VCC)
unnamed: JP12.2, LP18.1, LP18.2, SHIELD1.5V
unnamed: LP21.1, LP21.2, SHIELD1.RST
unnamed: LP25.2, SHIELD1.SCL1
unnamed: LP26.2, SHIELD1.SDA1
unnamed: LP27.1, LP27.2, SHIELD1.AREF
unnamed: P6.1, R4.1
unnamed: P6.3, R3.1
unnamed: P44.3, R15.2, R16.1, U9.1 (TX), U11.1 (TX)
unnamed: P45.3, P46.3, U10.7
unnamed: P45.4, P46.4, U10.6
unnamed: Q1.B, R18.2
unnamed: R5.1, SHIELD1.13
unnamed: R6.2, R7.1, U2.4 (RXD)
unnamed: R17.2, RV1.1, U4.1 (ADJ)
unnamed: R20.1, SHIELD1.7
unnamed: R21.1, SHIELD1.6
unnamed: R22.1, U2.6 (LED)
unnamed: R24.1, ZD1.1 (A)
unnamed: R25.1, ZD2.1 (A)
unnamed: R26.1, ZD3.1 (A)
unnamed: RP1.9 (R8), RR1.2, SHIELD1.AD0
unnamed: RP1.10 (R7), RR1.3, SHIELD1.AD1
unnamed: RP1.11 (R6), RR1.4, SHIELD1.AD2
unnamed: RP1.12 (R5), RR1.5, SHIELD1.AD3
unnamed: RP1.13 (R4), RR1.6, SHIELD1.AD4
unnamed: RP1.14 (R3), RR1.7, SHIELD1.AD5
unnamed: RP1.15 (R2), RR1.8, SHIELD1.AD6
unnamed: RP1.16 (R1), RR1.9, SHIELD1.AD7
unnamed: RP2.9 (R8), RR2.9, SHIELD1.AD8
unnamed: RP2.10 (R7), RR2.8, SHIELD1.AD9
unnamed: RP2.11 (R6), RR2.7, SHIELD1.AD10
unnamed: RP2.12 (R5), RR2.6, SHIELD1.AD11
unnamed: RP2.13 (R4), RR2.5, SHIELD1.AD12
unnamed: RP2.14 (R3), RR2.4, SHIELD1.AD13
unnamed: RP2.15 (R2), RR2.3, SHIELD1.AD14
unnamed: RP2.16 (R1), RR2.2, SHIELD1.AD15
unnamed: U1.3 (VIN), U5.5 (IP-), U6.3 (VIN), U7.3 (VIN)
Power: JP1.2, LP17.1, LP17.2, SHIELD1.V_IN
Power5: C3.1, C6.1, Dual1.3 (Vdd), Dual1.6 (M1nD2), Dual1.15 (M2nD2), Dual2.3 (Vdd), Dual2.15 (M2nD2), JP8.1, JP11.2, JP12.1, JP14.1, P1.1, P2.1, P3.1, P4.1, P5.1, P8.1, P9.1, P10.1, P12.1, P13.1, P14.1, P19.1, P21.1, P22.1, P23.1, P24.1, P25.1, P26.1, P27.1, P28.1, P29.1, P30.1, P31.1, P33.1, P33.2, P33.3, P33.4, P33.5, P33.6, P33.7, P33.8, P35.1, P40.1, P41.1, P44.1, P45.1, P46.1, R1.1, R8.2, R14.2, U3.1 (VCC), U5.1 (VCC), U8.3 (VCC), U10.1
PowerA3,3: JP3.2, JP15.1, LP16.1, LP16.2, SHIELD1.3V3
RX1: P44.4, R14.1, SHIELD1.19 (RX1), U9.8 (RX), U11.8 (RX)
RX2: R8.1, SHIELD1.17 (RX2), U2.3 (TXD)
ReserveAD6: LP6.1, LP6.2, P22.3, RP1.2
ReserveAD11: LP11.1, LP11.2, P4.3, RP2.5
ReservePin0: P27.3, SHIELD1.0 (RX0)
ReservePin1: P29.3, SHIELD1.1 (TX0)
ReservePin4: P26.3, SHIELD1.4
ReservePin8: P28.3, SHIELD1.8
ReservePin9: P25.3, SHIELD1.9
SCL2: P5.4, P23.4, P24.4, SHIELD1.21 (SCL), U8.5 (SCL), U10.2
SDA2: P5.3, P23.3, P24.3, SHIELD1.20 (SDA), U8.4 (SDA), U10.3
Spannungmessung: JP13.2, JP14.2, JP15.2, LP7.1, LP7.2, P14.3, RP1.1
StationLed: P7.5, R11.2
TX1: R15.1, SHIELD1.18 (TX1)
TX2: R6.1, SHIELD1.16 (TX2)
pinBatteryVoltage: LP2.1, LP2.2, R12.2, R13.1, RP1.6
pinBumperLeft: P11.4, SHIELD1.39 (PG2)
pinBumperRight: P11.3, SHIELD1.38 (PD7)
pinButton: P20.1, SHIELD1.51 (PB2_(MOSI))
pinBuzzer: SHIELD1.53 (PB0_(SS)), SP1.2
pinChargeCurrent: LP8.1, LP8.2, RP2.8, U3.3 (OUT)
pinChargeVoltage: LP9.1, LP9.2, R9.2, R10.1, RP2.7
pinChargingBalance: LP10.1, LP10.2, RP2.6, U5.3 (OUT)
pinChargingEnable: JP4.1, SHIELD1.50 (PB3_(MISO))
pinLawnBackRecv: P6.4, SHIELD1.42 (PL7)
pinLawnBackSend: R3.2, SHIELD1.43 (PL6)
pinLawnFrontRecv: P6.2, SHIELD1.40 (PG1)
pinLawnFrontSend: R4.2, SHIELD1.41 (PG0)
pinMotorEnable: Dual1.10 (EN), SHIELD1.37 (PC0)
pinMotorLeftDir: Dual1.4 (M1IN2), SHIELD1.31 (PC6)
pinMotorLeftFault: Dual1.8 (M1nSF), SHIELD1.25 (PA3)
pinMotorLeftPWM: Dual1.5 (M1IN1), SHIELD1.5
pinMotorLeftSense: Dual1.9 (M1FB), LP1.1, LP1.2, RP1.7
pinMotorMowDir: Dual2.13 (M2IN2), SHIELD1.29 (PA7)
pinMotorMowEnable: Dual2.10 (EN), SHIELD1.28 (PA6)
pinMotorMowFault: Dual2.17 (M2nSF), SHIELD1.26 (PA4)
pinMotorMowPWM: Dual2.14 (M2IN1), SHIELD1.2
pinMotorMowRpm: P35.3, SHIELD1.49 (PL0)
pinMotorMowSense: Dual2.18 (M2_FB), LP3.1, LP3.2, RP1.5
pinMotorRightDir: Dual1.13 (M2IN2), SHIELD1.33 (PC4)
pinMotorRightFault: Dual1.17 (M2nSF), SHIELD1.27 (PA5)
pinMotorRightPWM: Dual1.14 (M2IN1), SHIELD1.3
pinMotorRightSense: Dual1.18 (M2_FB), LP0.1, LP0.2, RP1.8
pinOdometryLeft: LP12.1, LP12.2, P9.3, RP2.4
pinOdometryLeft2: LP13.1, LP13.2, P9.4, RP2.3
pinOdometryRight: LP14.1, LP14.2, P8.3, RP2.2
pinOdometryRight2: LP15.1, LP15.2, P8.4, RP2.1
pinPerimeterLeft: LP5.1, LP5.2, P12.3, RP1.3
pinPerimeterRight: LP4.1, LP4.2, P30.3, RP1.4
pinRain: P41.3, SHIELD1.44 (PL5)
pinRemoteMow: P13.3, SHIELD1.12
pinRemoteSpeed: P13.5, SHIELD1.10
pinRemoteSteer: P13.4, SHIELD1.11
pinRemoteSwitch: P13.6, SHIELD1.52 (PB1_(SCK))
pinSonarCenterEcho: LP20.1, LP20.2, P1.4, SHIELD1.22 (PA0)
pinSonarCenterTrigger: P1.3, SHIELD1.24 (PA2)
pinSonarLeftEcho: LP23.1, LP23.2, P3.4, SHIELD1.36 (PC1)
pinSonarLeftTrigger: P3.3, SHIELD1.34 (PC3)
pinSonarRightEcho: LP22.1, LP22.2, P2.4, SHIELD1.32 (PC5)
pinSonarRightTrigger: P2.3, SHIELD1.30 (PC7)
pinTilt: P19.3, SHIELD1.35 (PC2)
pinUserSwitch1: P40.3, SHIELD1.46 (PL3)
pinUserSwitch2: P40.4, SHIELD1.47 (PL2)
pinUserSwitch3: P40.5, SHIELD1.48 (PL1)

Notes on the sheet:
Sonar HC SR-04
Perimeter coil
Lawn sensor
Tilt sensor
GPS
Bumper
Batterie
Pufferkondensator für Relaisumschaltung
Jumper Spannungsversorgung von Akku
Jumper Spannungsversorgung von über Relais
Jumper Relais Ein oder Ausschalten Ansteuerung durch Arduino
Jumper Relais Ein oder Ausschalten Ansteuerung durch Ladespannung
Laderelais Spulenspannung 5V oder Variabel Eingang Spulenspannung kann über Vorwiderspannung angepasst werden durch Ladespannung
Vorwiderstand Relais kann über ändern angepasst werden an verschiedene Ladespannung
Rückflussdiode Falls Ladeschaltung nicht benötigt Ladeschaltung nicht bestücken und für Diode Drahtbrücke einlöten
Anschlußklemme geändert + Duo LED hinzugefügt
Duo LED hinzugefügt
Station LED bzw: Grundlast Perimetersender
Strom von Relais muss vor der Diode geholt werden wenn nach Diode oderLM350T geholt wird geht das Relais rückwärt in Selbthaltung und kann nicht mehr abfallen
Hier 5V richtig??
Sperrdiode die die Rückwärtsspannung vermeidet wenn DC-DC wander von Ladestrom versorgt werden soll (@SteanM]
Rückflussdiode oder Lötbrücke um Leiterbahn zu Schließen falls LM350T nicht bestückt wird
Perimeter rechts auf Wunsch hinzugefügt
Abgriff 5V, 3V, GND
LED Anzeigen - Hardware: Led 3V grün - Betriebsanzeige Versorgungsspannung LED 24V grün - Betriebsanzeige Versorgungsspannung LED 5V grün - Betriebsanzeige Versorgungsspannung LED Station - gelb - Statusanzeige ob Mover in Ladestation ---------------------------------------------------------- LED A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
LED Rechner: http://www.elektronik-kompendium.de/sites/bau/1109111.htm Z-Dioden Rechner: http://www.dieelektronikerseite.de/Tools/Zenerdiode.htm

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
